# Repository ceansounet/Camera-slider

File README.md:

# Camera-Slider
This project is a camera slider, useful to take smooth video shots, long moving timelapses, repeatable movement for special effect shots and much more.

## Features : 
- 2 motors for translation and rotation
- Compatible with phone control and a custom controller
- Saving points and playing them back
- Custom speed curves
- A ton of possible shots : timelapse, special FX overlaying, object tracking.
- usb-c charging for both, the slider is compatible with any usb-c battery bank (~20W peak)

## Workflow :
- connect
- Set 2 points or more by hand
- choose speed curves (or leave the default one)
- choose the kind of shot wanted
- start recording
- press play

## here is a youtube playlist with all of my work sessions :
[Camera-Slider Playlist](https://www.youtube.com/watch?v=zh-EyJo-g44&list=PLc9wTLk_Nb17q8Yq_pcCUll0olrOZS_lk&pp=0gcJCcwEOCosWNinsAgC)

Main CAD file :

Cut view of the slider :

PCB for the slider :

Controller CAD :

Main PCB for the controller :

Second controller PCB : 

Exploded shot GIF for Assembly : 

## Tech used :

CAD - Solidworks + Grabcad

PCB - Kicad

Code - VScode + ESP IDF addon

## Videos and pictures of the build :

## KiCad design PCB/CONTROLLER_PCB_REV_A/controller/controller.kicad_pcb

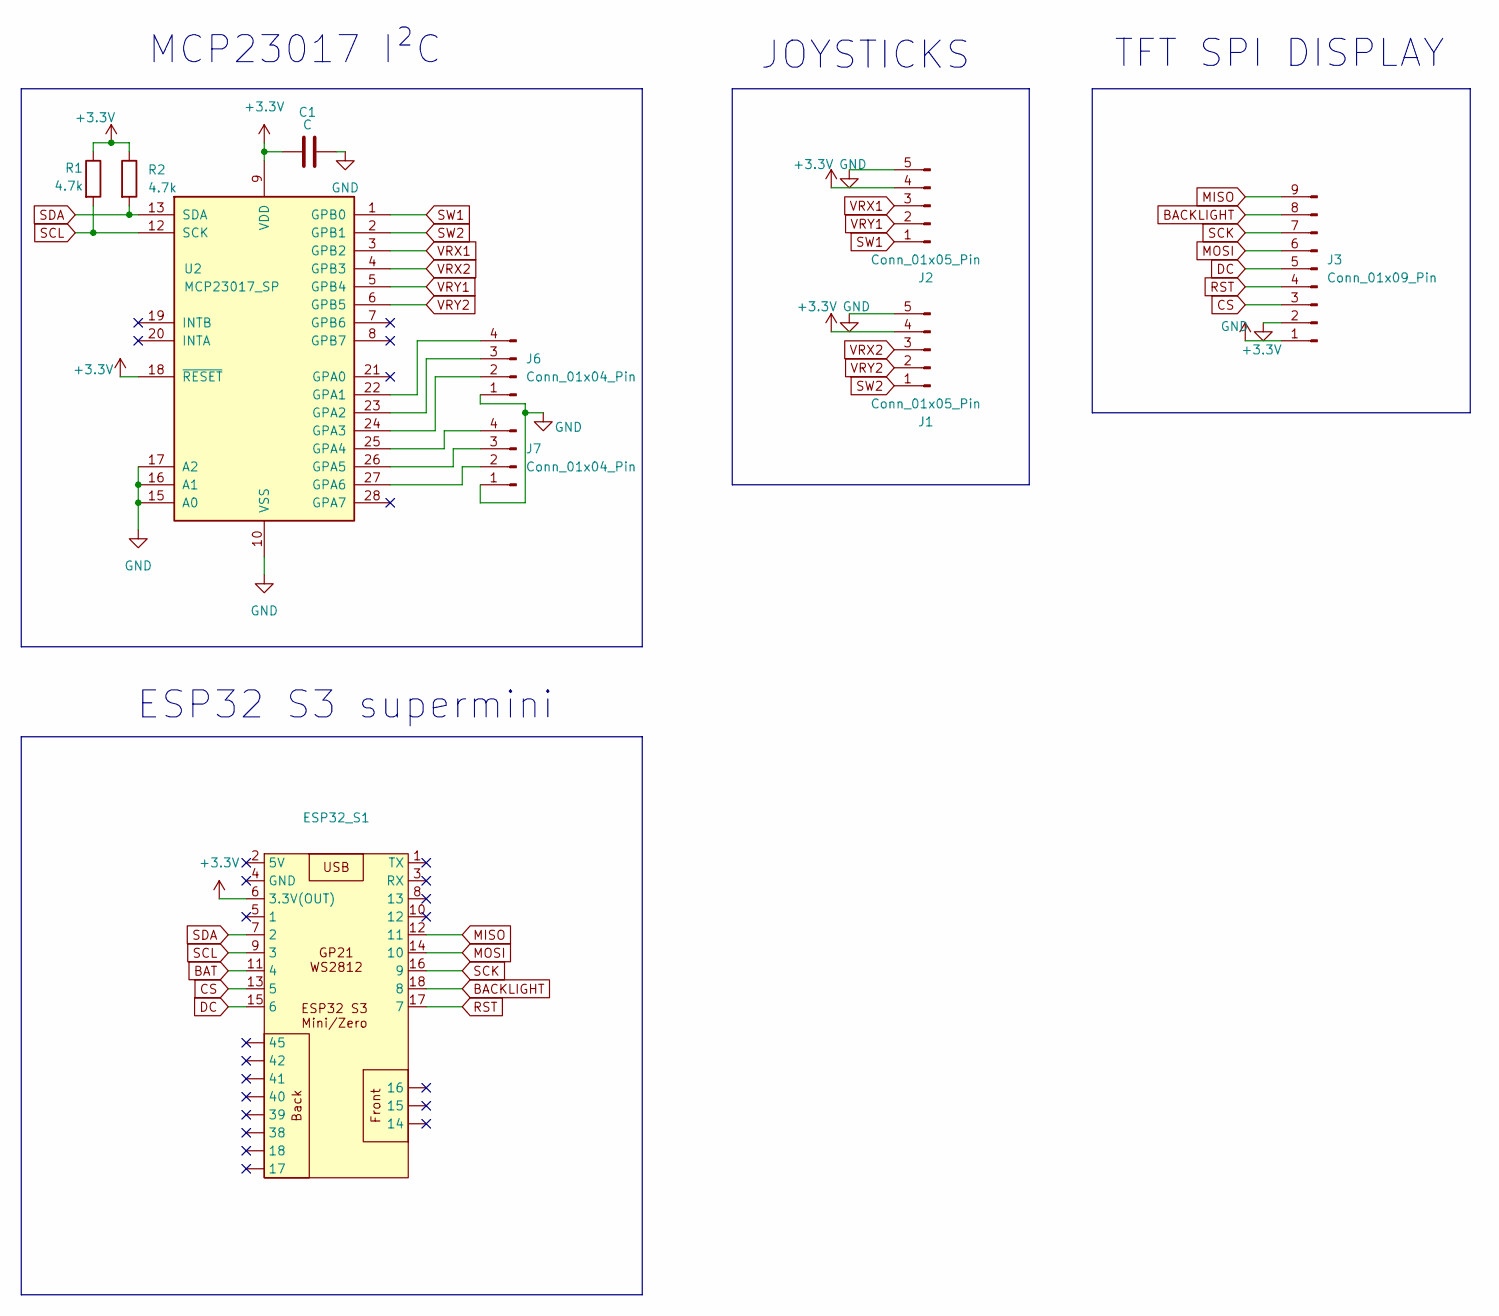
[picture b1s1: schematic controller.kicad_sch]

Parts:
C1: C; C_Disc_D5.0mm_W2.5mm_P5.00mm
ESP32_S1: ESP32-S3-MINI
J1, J2: Conn_01x05_Pin; PinHeader_1x05_P2.54mm_Vertical
J3: Conn_01x09_Pin; PinHeader_1x14_P2.54mm_Vertical
J6, J7: Conn_01x04_Pin; PinHeader_1x04_P2.54mm_Vertical
R1, R2: 4.7k; R_Axial_DIN0207_L6.3mm_D2.5mm_P7.62mm_Horizontal
U2: MCP23017_SP; DIP-28_W7.62mm

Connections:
+3.3V: C1.1, ESP32_S1.6 (3.3V(OUT)), J1.4, J2.4, J3.1, R1.1, R2.1, U2.9 (VDD), U2.18 (~RESET)
BACKLIGHT: ESP32_S1.18 (8), J3.8
BAT: ESP32_S1.11 (4)
CS: ESP32_S1.13 (5), J3.3
DC: ESP32_S1.15 (6), J3.5
GND: C1.2, J1.5, J2.5, J3.2, J6.1, J7.1, U2.10 (VSS), U2.15 (A0), U2.16 (A1), U2.17 (A2)
MISO: ESP32_S1.12 (11), J3.9
MOSI: ESP32_S1.14 (10), J3.6
unnamed: J6.2, U2.24 (GPA3)
unnamed: J6.3, U2.23 (GPA2)
unnamed: J6.4, U2.22 (GPA1)
unnamed: J7.2, U2.27 (GPA6)
unnamed: J7.3, U2.26 (GPA5)
unnamed: J7.4, U2.25 (GPA4)
RST: ESP32_S1.17 (7), J3.4
SCK: ESP32_S1.16 (9), J3.7
SCL: ESP32_S1.9 (3), R1.2, U2.12 (SCK)
SDA: ESP32_S1.7 (2), R2.2, U2.13 (SDA)
SW1: J2.1, U2.1 (GPB0)
SW2: J1.1, U2.2 (GPB1)
VRX1: J2.3, U2.3 (GPB2)
VRX2: J1.3, U2.4 (GPB3)
VRY1: J2.2, U2.5 (GPB4)
VRY2: J1.2, U2.6 (GPB5)

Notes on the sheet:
ESP32 S3 supermini
TFT SPI DISPLAY
JOYSTICKS
MCP23017 I²C

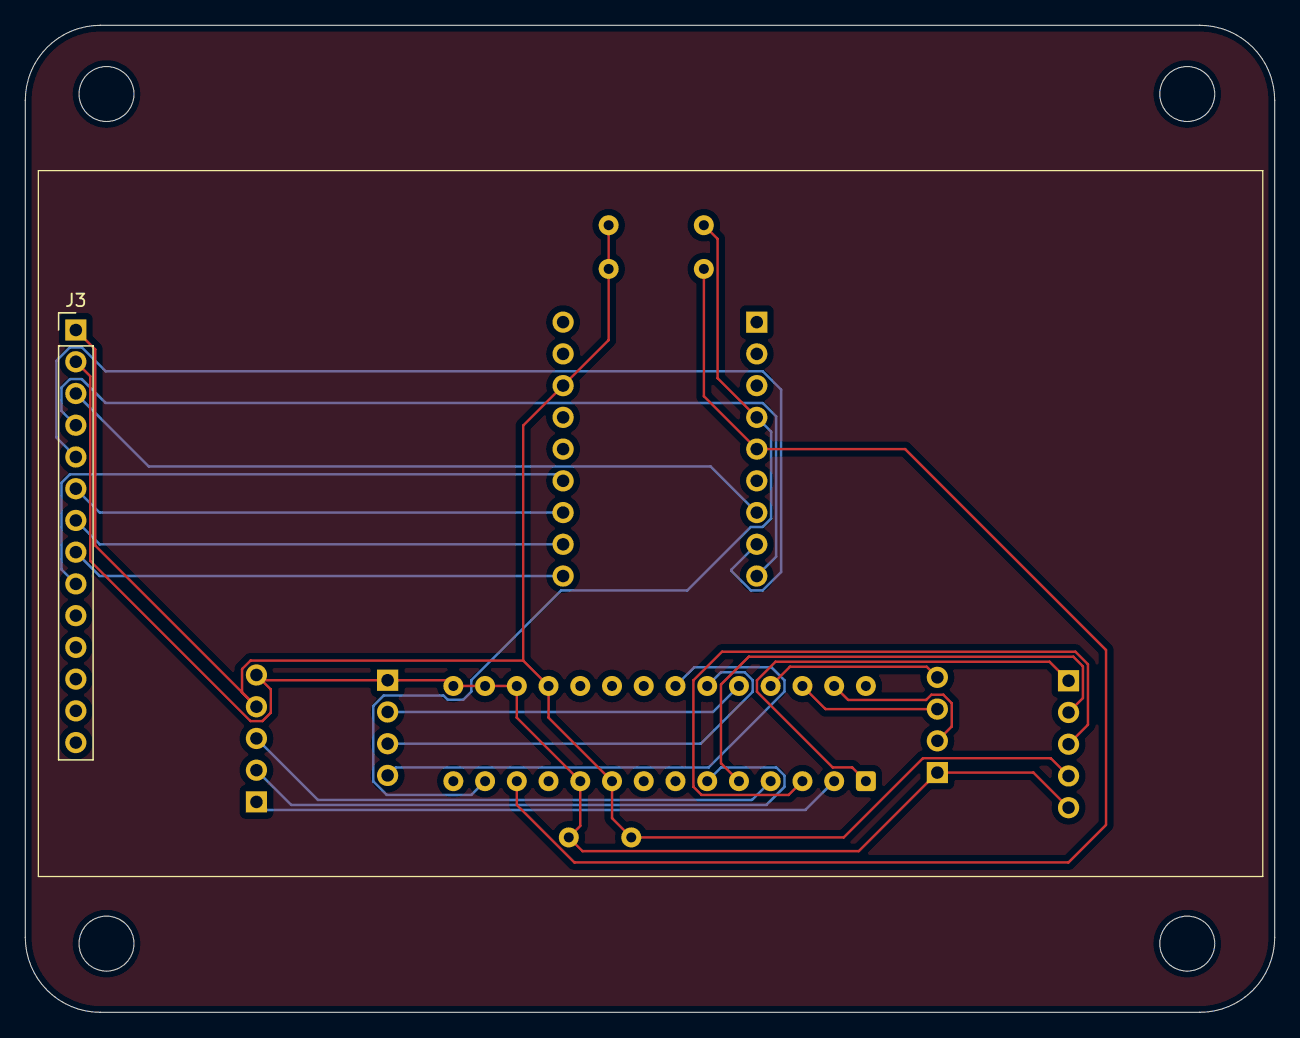
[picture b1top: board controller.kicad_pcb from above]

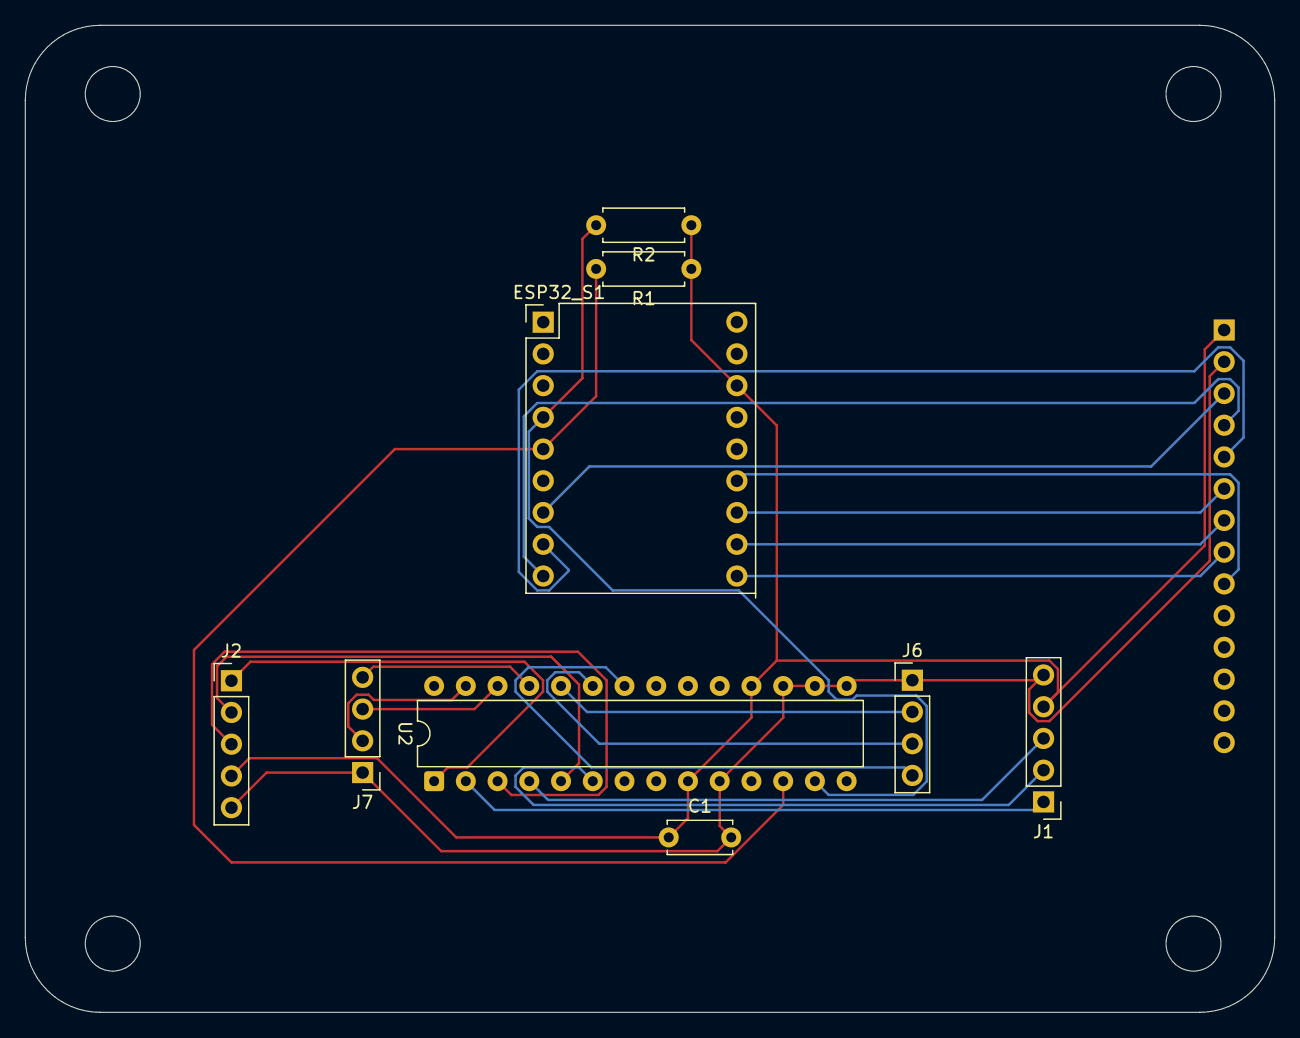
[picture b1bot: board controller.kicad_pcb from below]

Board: 2 copper layers, 100.0 x 79.0 mm, 10 parts (9 on the bottom side), 23 nets.

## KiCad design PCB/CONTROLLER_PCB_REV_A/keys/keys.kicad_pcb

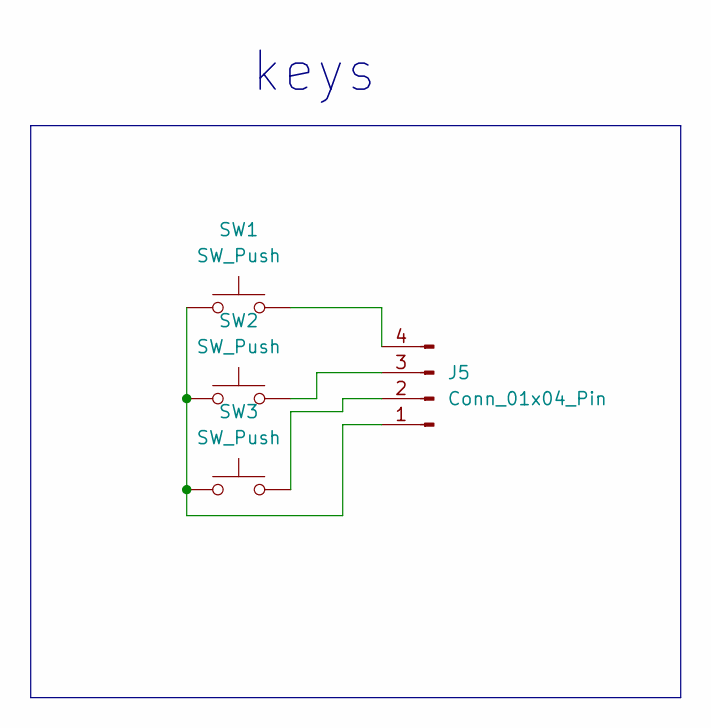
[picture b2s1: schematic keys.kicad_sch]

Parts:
J5: Conn_01x04_Pin; PinHeader_1x04_P2.54mm_Horizontal
SW1, SW2, SW3: SW_Push; SW_Cherry_MX_1.00u_PCB

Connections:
unnamed: J5.1, SW1.1, SW2.1, SW3.1
unnamed: J5.2, SW3.2
unnamed: J5.3, SW2.2
unnamed: J5.4, SW1.2

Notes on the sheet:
keys

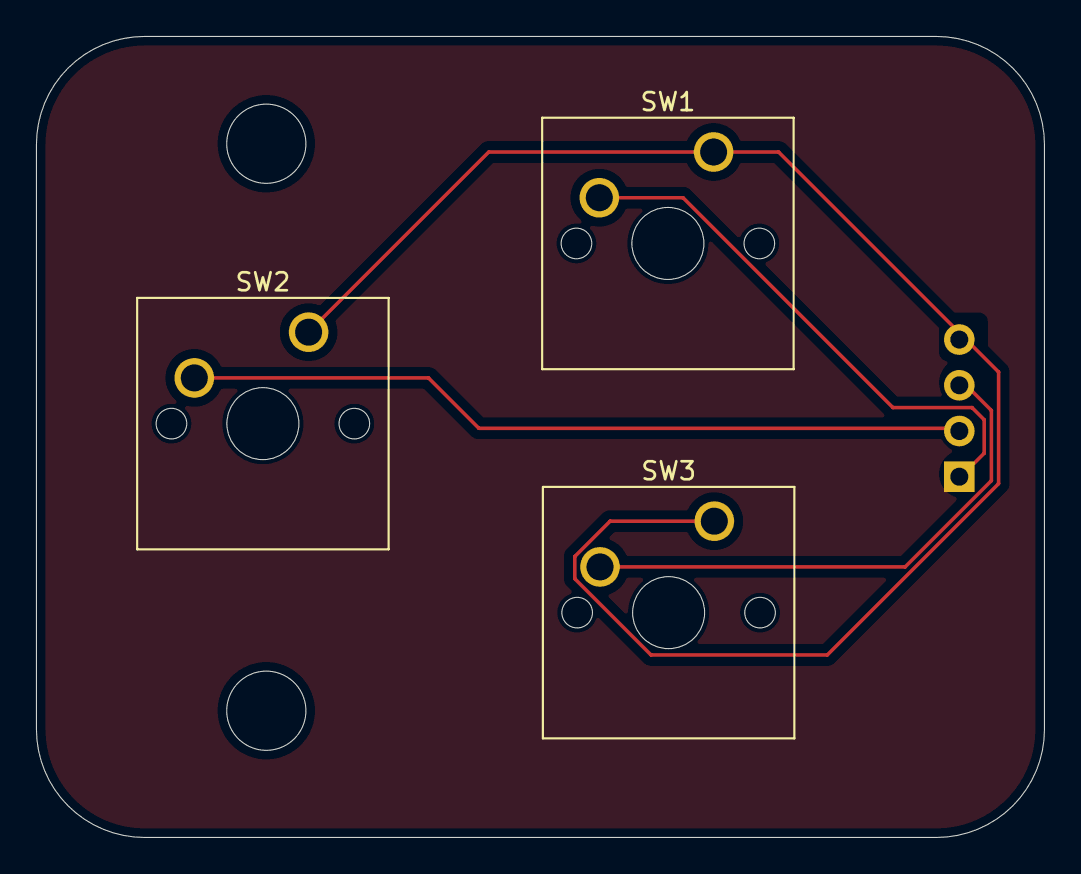
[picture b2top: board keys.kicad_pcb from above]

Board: 2 copper layers, 56.0 x 44.5 mm, 4 parts (1 on the bottom side), 4 nets.

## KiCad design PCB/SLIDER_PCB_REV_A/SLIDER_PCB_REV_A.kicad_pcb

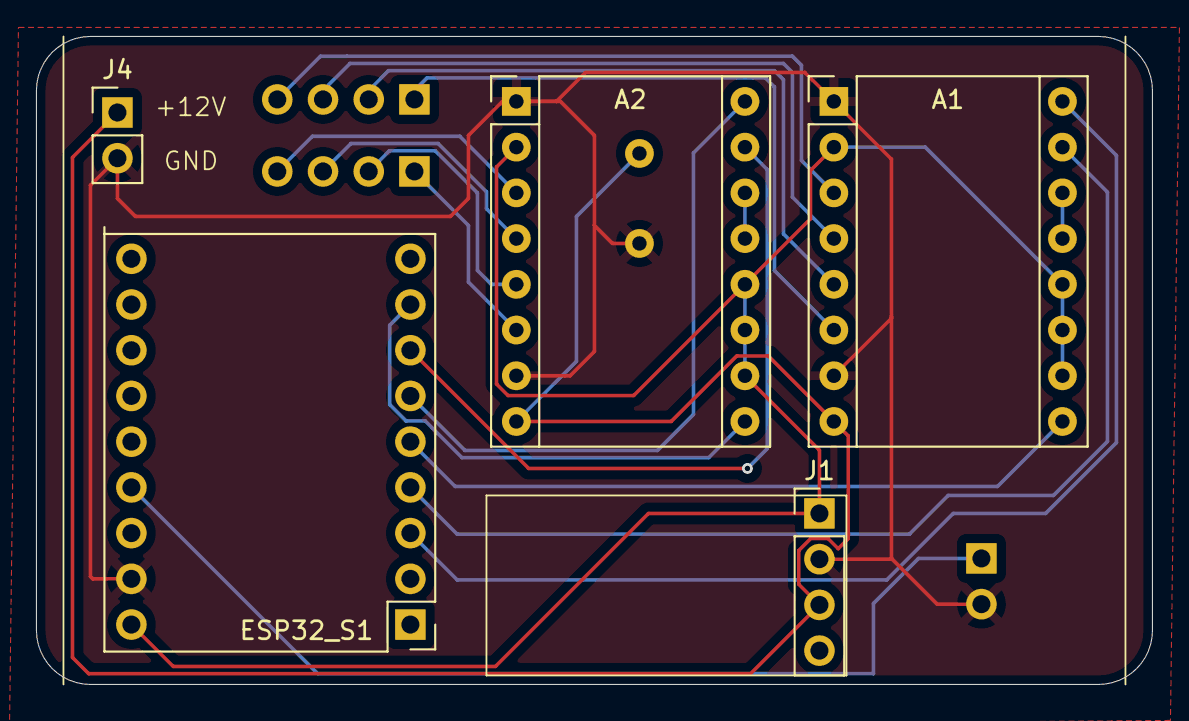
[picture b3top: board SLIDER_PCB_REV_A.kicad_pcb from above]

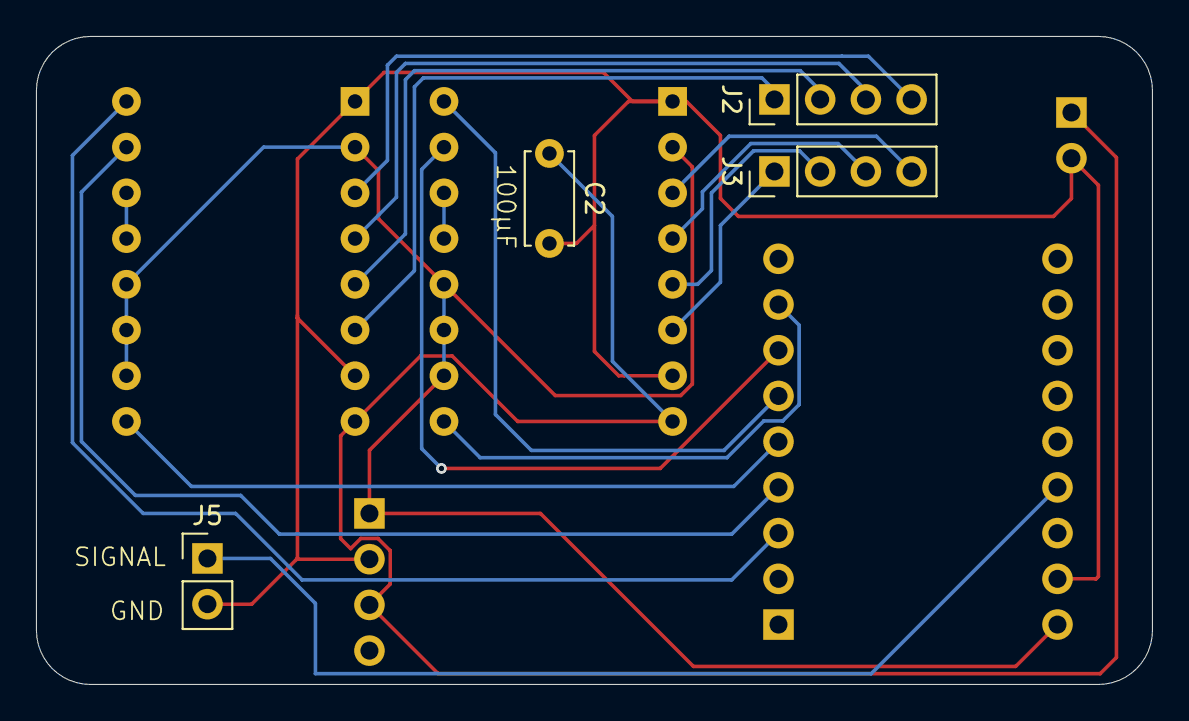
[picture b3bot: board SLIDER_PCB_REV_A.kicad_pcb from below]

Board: 2 copper layers, 62.0 x 36.0 mm, 9 parts (4 on the bottom side), 20 nets.

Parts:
A1, A2: Pololu_Breakout_A4988; Pololu_Breakout-16_15.2x20.3mm
C2: C_Polarized; C_Disc_D5.0mm_W2.5mm_P5.00mm
ESP32_S1: PinHeader_2x09_P2.54mm_Vertical
J1, J2, J3: V0; PinHeader_1x04_P2.54mm_Vertical
J4, J5: Conn_01x02_Pin; PinHeader_1x02_P2.54mm_Vertical

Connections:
+12V: A1.8 (VMOT), A2.8 (VMOT), C2.1, J1.3 (IN+), J4.1
GND: A1.1 (GND), A1.7 (GND), A2.1 (GND), A2.7 (GND), C2.2, ESP32_S1.4 (GND), J1.2 (GND), J4.2, J5.2
unnamed: A1.4 (1A), J2.3 (IN+)
unnamed: A1.3 (1B), J2.4 (EN)
unnamed: A1.5 (2A), J2.2 (GND)
unnamed: A1.6 (2B), J2.1 (V0)
unnamed: A1.16 (DIR), ESP32_S1.5 (1)
unnamed: A1.15 (STEP), ESP32_S1.7 (2)
unnamed: A1.9 (~ENABLE), ESP32_S1.9 (3)
unnamed: A1.13 (~RESET), A1.14 (~SLEEP)
unnamed: A2.4 (1A), J3.3 (IN+)
unnamed: A2.3 (1B), J3.4 (EN)
unnamed: A2.5 (2A), J3.2 (GND)
unnamed: A2.6 (2B), J3.1 (V0)
unnamed: A2.16 (DIR), ESP32_S1.11 (4)
unnamed: A2.15 (STEP), ESP32_S1.13 (5)
unnamed: A2.9 (~ENABLE), ESP32_S1.15 (6)
unnamed: A2.13 (~RESET), A2.14 (~SLEEP)
unnamed: ESP32_S1.8 (13), J5.1
VDD: A1.2 (VDD), A1.10 (MS1), A1.11 (MS2), A1.12 (MS3), A2.2 (VDD), A2.10 (MS1), A2.11 (MS2), A2.12 (MS3), ESP32_S1.2 (5V), J1.1 (V0)

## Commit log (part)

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2026-04-25 First commit, 18hrs of work; Only CAD and PCB.
2026-04-25 21h30 update : cad and PCB changes
2026-05-07 Added the whole controller PCB and CAD, plus some minor CAD changes, and a frog sticker asset for the controller.
2026-05-07 Minor cad changes on the controller, added placeholder files in firmware, and moved some stuff around.
2026-05-29 Created journal.md
2026-05-29 Transfered journal (mostly) from fallout manually
2026-05-31 Update journal.md
    added the pictures
2026-05-31 Update README.md
    added youtube playlist
2026-06-01 Update README.md
    Added title and description
2026-06-01 Update README.md
    added the README stuff in the guide from stardance
2026-06-11 Added 3d print files, BOM, and other stuff
2026-06-12 Changed BOM Added 3mf project files for the 3d prints
2026-06-12 added blender files added full step assemblies
2026-06-12 Update README.md
    Added PCB buttons
2026-06-12 Update journal.md
    added last 2 days
2026-06-12 Updated firmware
